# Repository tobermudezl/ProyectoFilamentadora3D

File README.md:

# ProyectoFilamentadora3D
Proyecto para la materia de Taller de Ingenieria Electronica.

# Integrantes 
Tomás Bermudez Lozano         | tobermudezl@unal.edu.co 

Juan Esteban Martinez Leon    | jumartinezle@unal.edu.co

Brayan Santiago Celi Almanza  | bceli@unal.edu.co

Johan Steven Ruiz Arango      | joruizar@unal.edu.co

# Descripción

Nuestro Proyecto tiene como fin de usar plastico reciclado filetiado (crear tiras homogeneas de plastico PET) por el usuario con el fin de crear filamento 3D con un prototipo economico y rentable para quienes quieran idearlo. Principalmente fue pensado para un consumo y reutilizacion eficaz de nuestros desechos plasticos. Los mismos desechos que se demoran al rededor de 300 o 400 años en descomponerse completamente. Aprovechando ese "problema" podemos verlo como una solucion eficaz para crear objetos en plastico resistentes, duraderos y amigables con el medio ambiente. Es un prototipo que tiene planeado ser implementado cerca de las salas con impresoras 3D con el fin que loe estudiantes puedan usar sus propias botellas plasticas recicladas y previamente fileteadas para poder ser introducidas por el prototipo y previamente usar el filamento 3D para sus proyectos.

# Problematica 

En Bogotá, la situación de los residuos plásticos es un desafío que afecta a todos. A medida que la ciudad crece y se urbaniza, también lo hacen los desechos plásticos, los cuales terminan, en su mayoría, en vertederos, ríos o incluso en las calles, generando problemas de contaminación que afectan la salud y el bienestar de los bogotanos. Aunque se han realizado esfuerzos por mejorar la gestión de residuos, todavía muy poco de lo que se produce se recicla correctamente, lo que agrava la situación y contribuye al cambio climático.
Por otro lado, la impresión 3D, que está ganando terreno en Bogotá, ofrece un sinfín de posibilidades en áreas como la educación, la construcción y la innovación tecnológica. Sin embargo, esta tecnología depende de filamentos plásticos, los cuales, en su mayoría, provienen de materiales nuevos, lo que continúa alimentando la demanda de recursos no sostenibles y aumentando el impacto ambiental. Aunque existen algunas alternativas de reciclaje, las tecnologías actuales para convertir los plásticos en nuevos productos no se han masificado por su alto costo y lo complejas que son de implementar. Es aquí donde surge una gran oportunidad: crear soluciones innovadoras que no solo ayudan a reducir los residuos plásticos, sino que también promuevan un uso más responsable de estos materiales, especialmente en áreas como la impresión 3D. Imaginemos una máquina capaz de transformar los plásticos que generamos en filamentos reciclados que puedan ser utilizados nuevamente para crear productos. Esta máquina no solo ayudaría a disminuir la cantidad de plásticos que terminan en vertederos, sino que también contribuiría a crear un ciclo de reutilización, donde los plásticos reciclados puedan tener una nueva vida, reduciendo la necesidad de plásticos vírgenes.
El agregado de un sistema de monitoreo en tiempo real permitiría controlar el proceso de reciclaje, asegurando que el filamento reciclado cumpla con los estándares necesarios para su uso en impresión 3D. Esto garantizaría que, incluso con plásticos reciclados, se mantuviera la calidad y funcionalidad del material. Implementar esta solución en Bogotá tendría múltiples beneficios. Por un lado, ayudaría a disminuir la cantidad de plástico desperdiciado que afecta tanto al medio ambiente como a la calidad de vida de los ciudadanos. Además, al reutilizar estos materiales, contribuiremos al cuidado del entorno y a reducir el impacto ambiental de la ciudad. Pero no solo eso, también abriría nuevas oportunidades de negocio, generando empleo en áreas como el reciclaje y la producción de materiales ecológicos. De esta manera, Bogotá podría fortalecer su compromiso con la sostenibilidad y avanzar hacia un futuro más verde y responsable.
Con proyectos como este, Bogotá podría dar un gran paso hacia un modelo más sostenible, no solo para enfrentar los problemas de los plásticos, sino para transformar la ciudad en un referente de innovación ambiental. Al integrar tecnologías como el reciclaje inteligente y la producción de filamentos reciclados, podríamos crear una economía más circular, generar empleo y, lo más importante, mejorar la calidad de vida para todos los bogotanos

# Objetivos 

Desarrollar un prototipo de filamentadora con método de extrusión sostenible a partir de residuos plásticos PET, que integre un sistema de monitoreo en tiempo real basado en IoT para garantizar la calidad del filamento producido, contribuyendo a la economía circular y la sostenibilidad ambiental.

# Objetivos Especifico

..* Diseñar el prototipo de la filamentadora con sistema de extrusión para el reciclaje de plásticos PET. 
..* Implementar un sistema de monitoreo en tiempo real mediante sensores IoT para la supervisión de la temperatura
..* Evaluar la calidad del filamento producido en términos de uniformidad, resistencia y viabilidad para la impresión 3D.
..* Desarrollar una interfaz gráfica para la visualización remota de los datos obtenidos por los sensores. 
..* Promover la conciencia ambiental sobre la reutilización de residuos plásticos a través de la demostración y divulgación del prototipo.

# Cronograma

# Poster
![Poster]

# Producto Final

![Video Producto Final]

# Palabras Claves

Prototipos, Plastico reciclado, filamentadora, universidad, PET, plastico, reciclaje, medio ambiente.

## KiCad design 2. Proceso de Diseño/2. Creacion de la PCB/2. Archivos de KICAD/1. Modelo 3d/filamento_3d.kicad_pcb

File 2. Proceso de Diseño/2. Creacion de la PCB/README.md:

#  Informacion de la PCB

Una PCB de 9x9, una capa, tarjeta de fibra, antisolder, serigrafia.

Se ponen en esta carpeta las librerias usadas, los archivos completos del proyecto en KiCad.

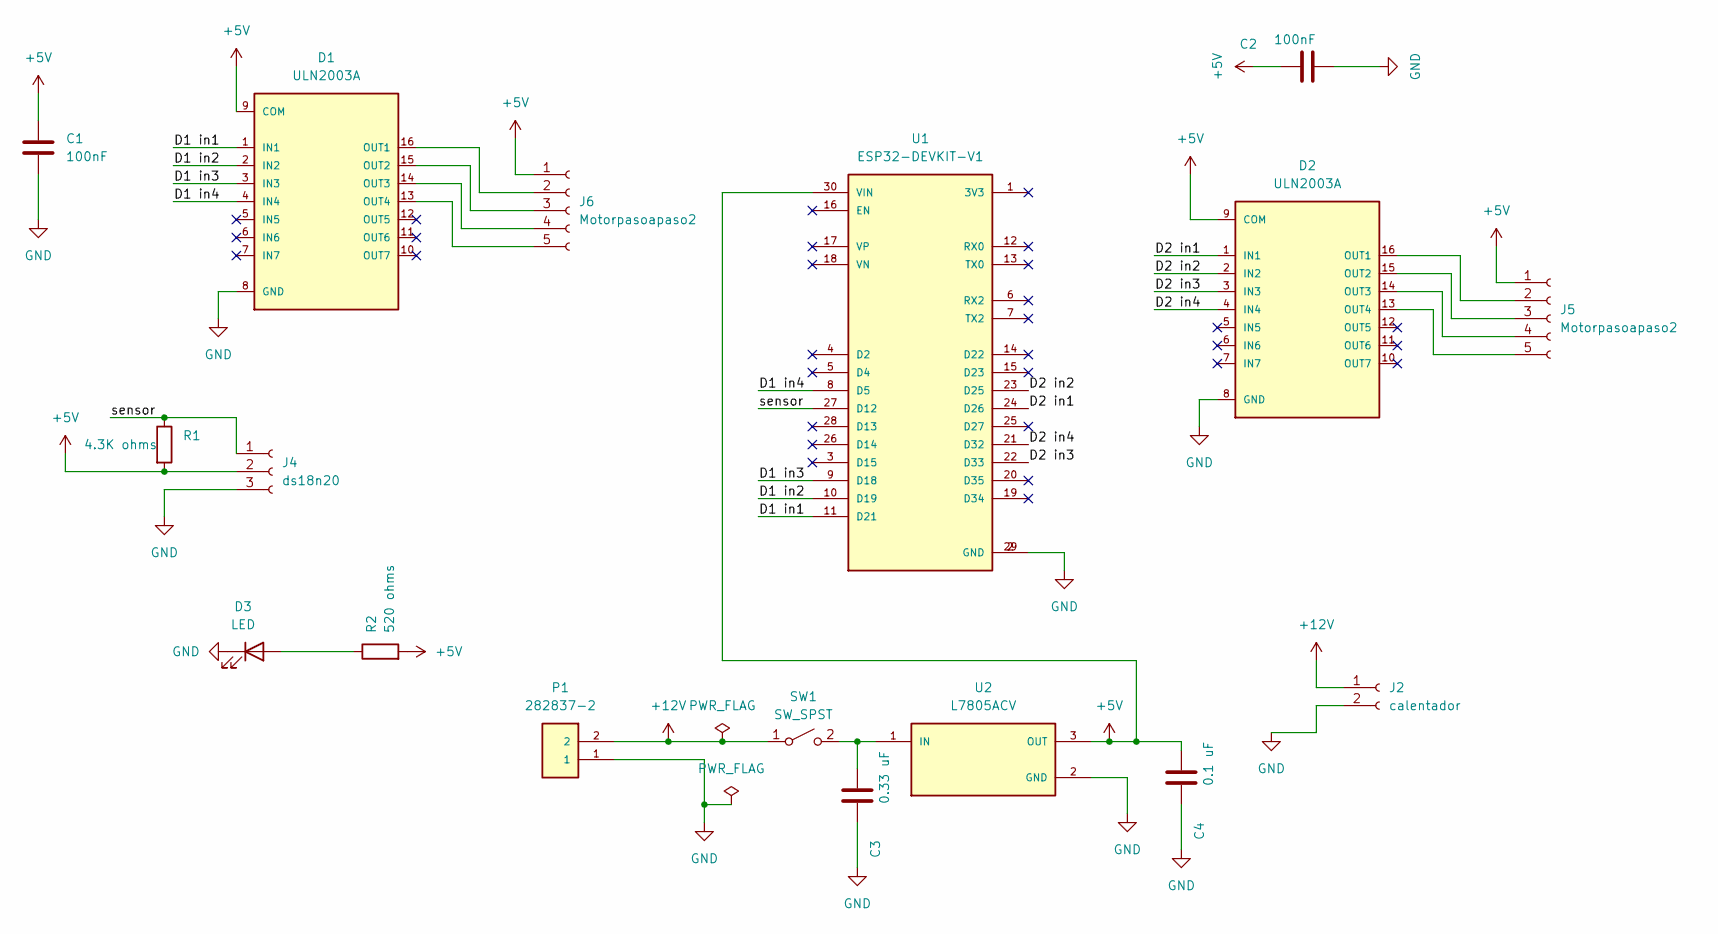
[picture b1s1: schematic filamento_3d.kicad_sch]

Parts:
C1, C2: 100nF; C_Disc_D3.8mm_W2.6mm_P2.50mm
C3: 0.33 uF; C_Disc_D3.8mm_W2.6mm_P2.50mm
C4: 0.1 uF; C_Disc_D3.8mm_W2.6mm_P2.50mm
D1, D2: ULN2003A; DIP254P762X445-16
D3: LED; LED_D2.0mm_W4.8mm_H2.5mm_FlatTop
J2: calentador; SolderWire-0.75sqmm_1x02_P4.8mm_D1.25mm_OD2.3mm
J4: ds18n20; PinHeader_1x03_P2.54mm_Vertical
J5, J6: Motorpasoapaso2; PinHeader_1x05_P2.00mm_Vertical
P1: 282837-2; TE_282837-2; PARTREV G3
R1: 4.3K ohms; R_Axial_DIN0204_L3.6mm_D1.6mm_P7.62mm_Horizontal
R2: 520 ohms; R_Axial_DIN0204_L3.6mm_D1.6mm_P7.62mm_Horizontal
SW1: SW_SPST; SolderWire-0.75sqmm_1x02_P4.8mm_D1.25mm_OD2.3mm
U1: ESP32-DEVKIT-V1; MODULE_ESP32_DEVKIT_V1; PARTREV N/A
U2: L7805ACV; TO254P460X1020X1945-3P

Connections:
+5V: C1.1, C2.1, C4.1, D1.9 (COM), D2.9 (COM), J4.2, J5.1, J6.1, R1.2, R2.2, U1.30 (VIN), U2.3 (OUT)
+12V: J2.1, P1.2, SW1.1 (A)
/D1 in1: D1.1 (IN1), U1.11 (D21)
/D1 in2: D1.2 (IN2), U1.10 (D19)
/D1 in3: D1.3 (IN3), U1.9 (D18)
/D1 in4: D1.4 (IN4), U1.8 (D5)
/D2 in1: D2.1 (IN1), U1.24 (D26)
/D2 in2: D2.2 (IN2), U1.23 (D25)
/D2 in3: D2.3 (IN3), U1.22 (D33)
/D2 in4: D2.4 (IN4), U1.21 (D32)
/sensor: J4.1, R1.1, U1.27 (D12)
GND: C1.2, C2.2, C3.2, C4.2, D1.8 (GND), D2.8 (GND), D3.1 (K), J2.2, J4.3, P1.1, U1.2 (GND), U1.29 (GND), U2.2 (GND)
unnamed: D1.16 (OUT1), J6.2
unnamed: D1.15 (OUT2), J6.3
unnamed: D1.14 (OUT3), J6.4
unnamed: D1.13 (OUT4), J6.5
unnamed: D2.16 (OUT1), J5.2
unnamed: D2.15 (OUT2), J5.3
unnamed: D2.14 (OUT3), J5.4
unnamed: D2.13 (OUT4), J5.5
unnamed: D3.2 (A), R2.1
unnamed: C3.1, SW1.2 (B), U2.1 (IN)

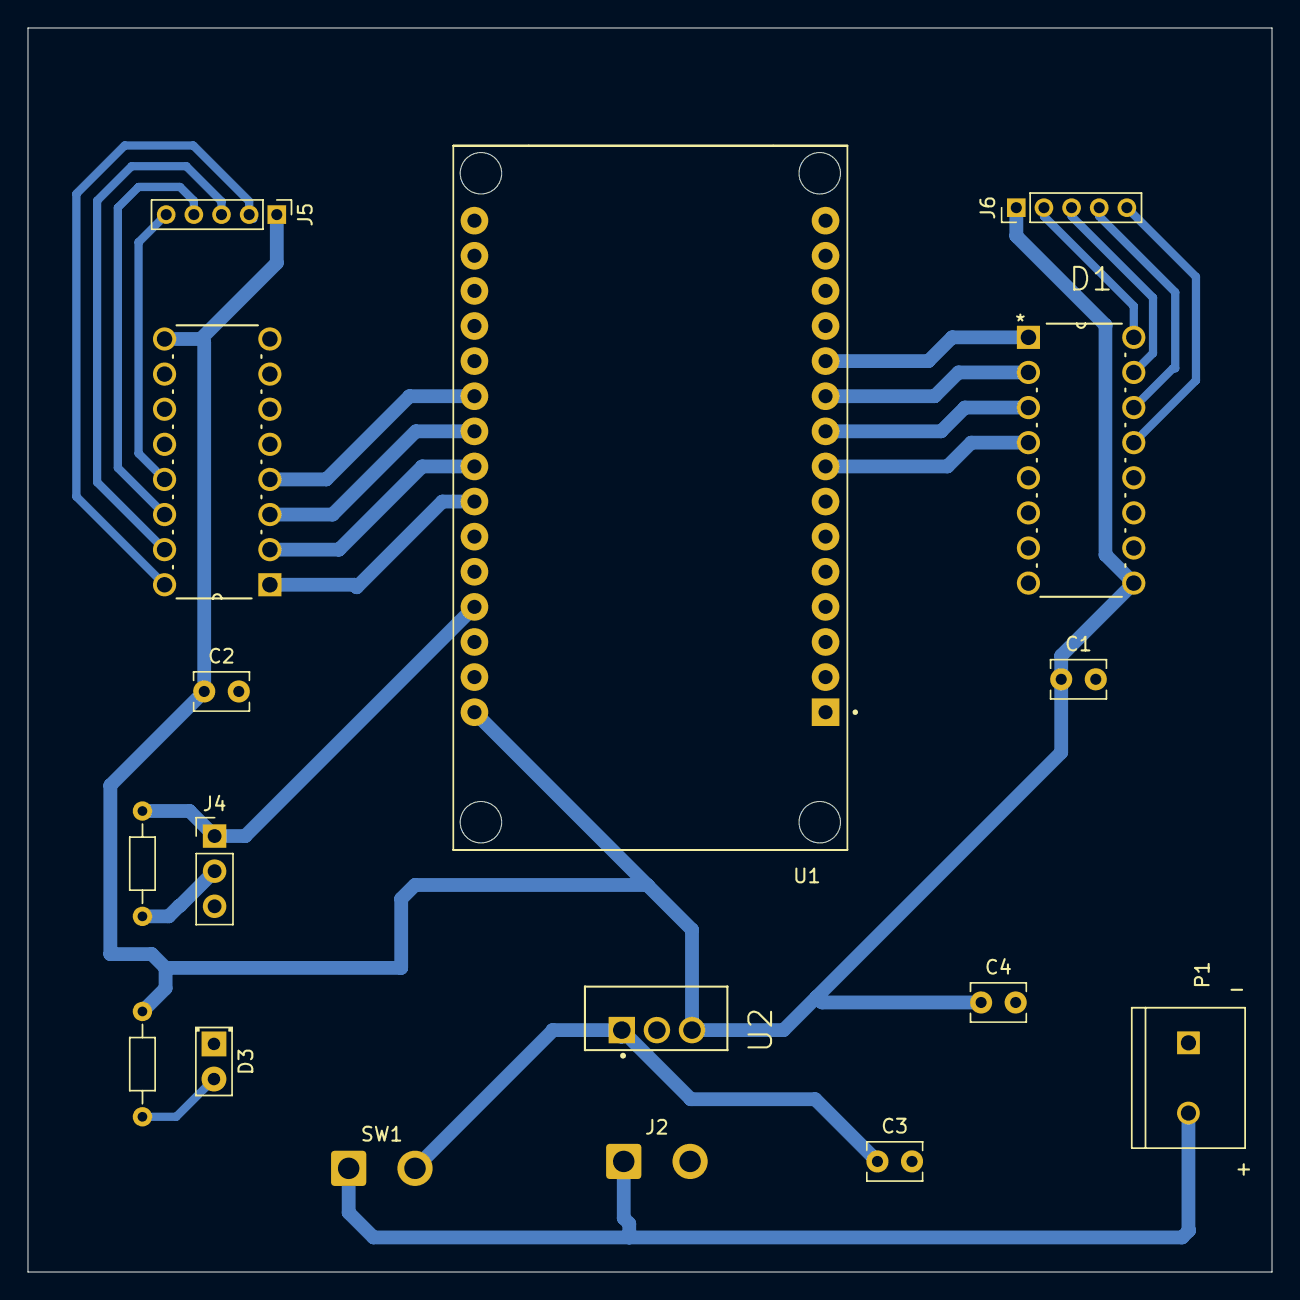
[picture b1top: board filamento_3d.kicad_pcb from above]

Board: 2 copper layers, 90.0 x 90.0 mm, 17 parts (0 on the bottom side), 22 nets.
